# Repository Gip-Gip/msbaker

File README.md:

**Ms. Baker is a compact microcomputer built off the RP2040, specifically with model rocketry in mind.**
Occupying a footprint under 10cm&sup2;, this computer provides a unique density of many useful components, including a compact **25 pin GPIO** connector and a high accuracy **IMU**.
These features in a compact and light package is especially useful for low and medium power rockets, but may also find use in other applications where an ultra-small microcomputer may be needed.

## Feature Set

Ms. Baker is fairly feature packed for the size, and includes:

### RP2040 MCU

Powered by Raspberry Pi's RP2040 Microcontroller, Ms. Baker has the computation power of a 133MHz dual-core Arm Corted-M0+ processor in an unbelievably compact package.

### Micro SD Card Slot

Useful for logging data and loading/storing programs, Ms. Baker comes equipped with a compact MicroSD card slot for easy-to-use data storage.

### I2C IMU

No rocket computer should be complete with at least some form of telemetry, and Ms. Baker comes with the versitile LSM6DSO32 IMU, providing both gyro and acceleration data at a sample rate of up to 6.7kHz.
It has a maximum measurable acceleration range of &plusmn;32*g* and a maximum measurable angular rate of &plusmn;200dps, which should be good for most low and medium powered rockets, in theory.

### USB Programmable ROM

Thanks to the RP2040 Ms. Baker is entirely programmable via USB, meaning so long as you have a Micro USB cable and a computer you have access to **16MBytes of ROM** with no extra hardware!

### GPIO

Utilizing a Molex SlimStack connector Ms. Baker provides 25 pins of GPIO in a very compact footprint, completely up for any use the end user may desire!

### Robust Firmware

Like any other OpenApeShop project, Ms Baker's firmware is *(to be written)* in the Rust programming language, making it very robust and resistant to common bugs that may occur in other embedded firmware solutions.

## Development Status

**With a working prototype**, Ms. Baker is on it's third prototype and has the following steps that need to be completed before it is more or less ready for use:

- [ ] Program the firmware so that by default Ms. Baker acts as a telemetry logging device
- [ ] Field test Ms. Baker on a live rocket
- [ ] Reorganize PCB to fill up any unused space by
    - [ ] Spacing traces to reduce the chances of crosstalk, when possible
    - [ ] Increasing the size of traces to reduce impedence, when possible
- [ ] Document Ms. Baker so it's easy to use
- [ ] Develop a pin breakout board so prototyping is as easy as with a normal Raspberry Pi Pico

## Legal

Ms Baker's hardware is under the CERN-OHL-S and software under GPL-3.0.
See LEGAL-HARDWARE for all legal info regarding hardware, LEGAL-SOFTWARE for all legal info regarding software.

## Links

* [Website](https://openapeshop.org/hardware/msbaker)
* [Schematic](https://github.com/Gip-Gip/msbaker/raw/main/docs/Renders/schematic.png)

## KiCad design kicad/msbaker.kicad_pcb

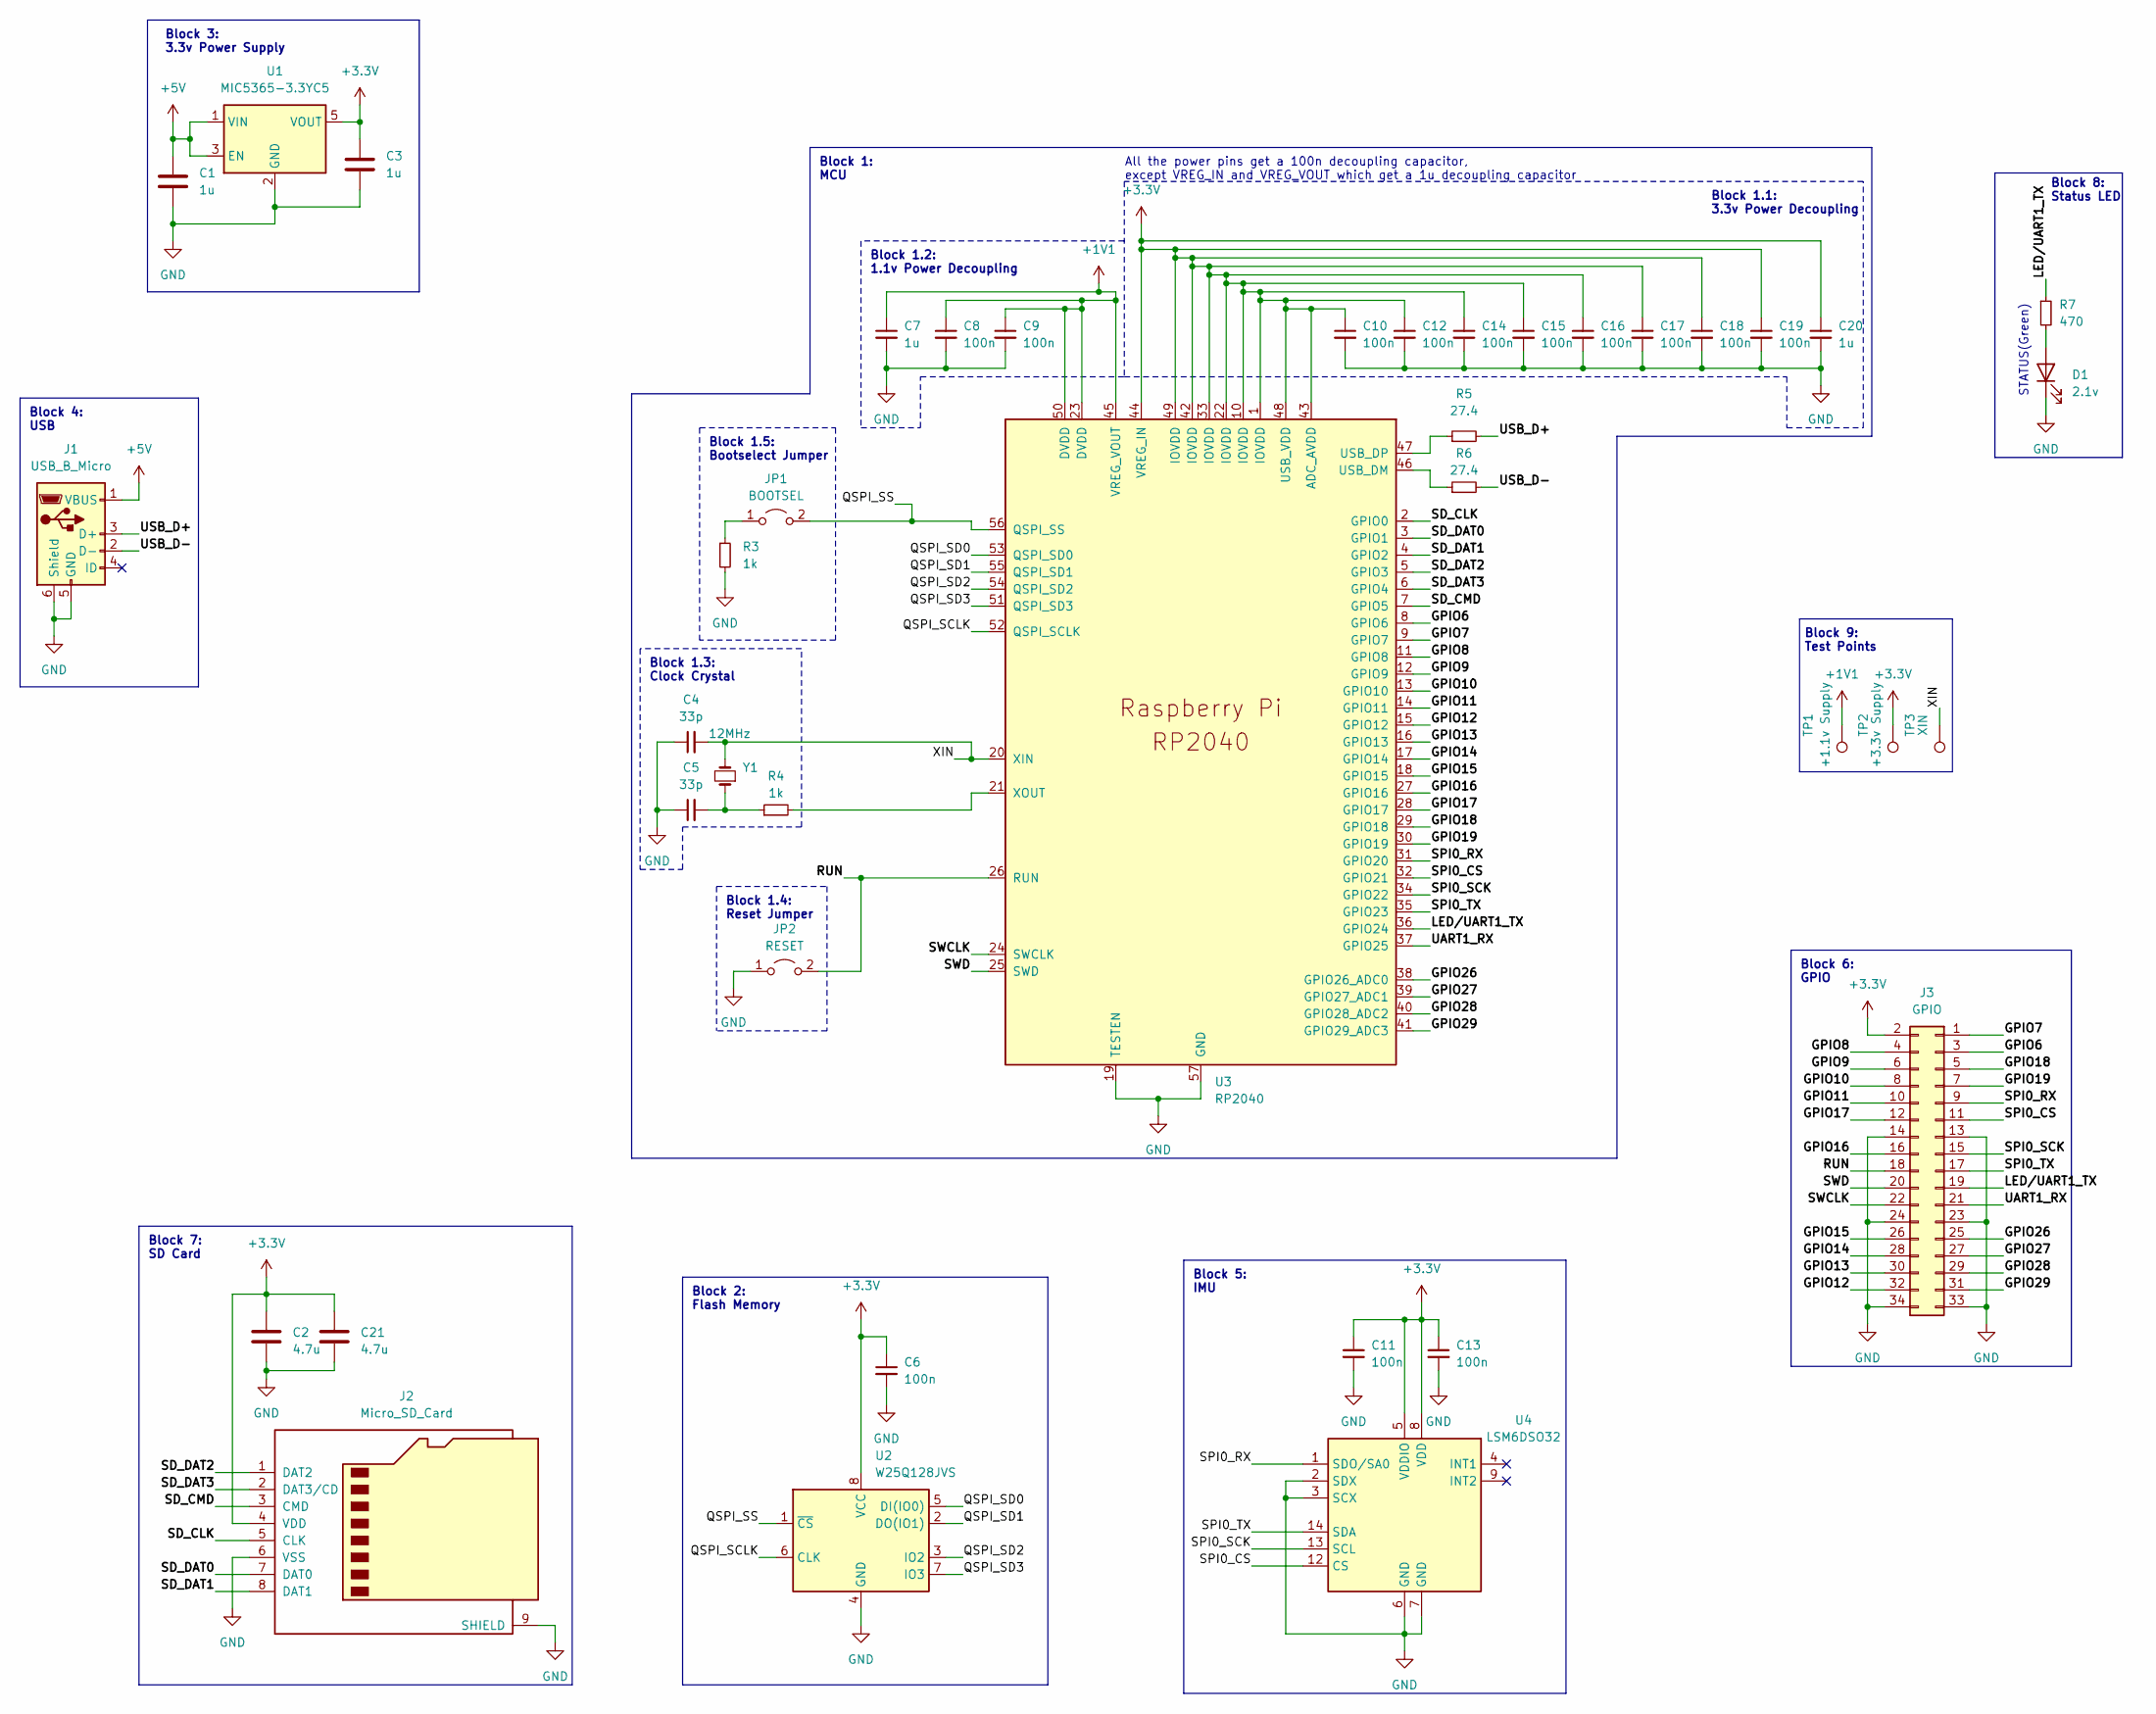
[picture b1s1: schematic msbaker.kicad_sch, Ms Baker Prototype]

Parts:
C1, C3, C7, C20: 1u; C_0402_1005Metric; MPN C1005X5R1E105K050BE
C2, C21: 4.7u; C_0402_1005Metric; MPN C1005X5R1A475K050BE
C4, C5: 33p; C_0402_1005Metric; MPN CGA2B2C0G1H330J050BA
C6, C8, C9, C10, C11, C12, C13, C14, C15, C16, C17, C18, C19: 100n; C_0402_1005Metric; MPN C1005X7R1H104K050BE
D1: 2.1v; LED_0402_1005Metric; MPN APHHS1005CGCK
J1: USB_B_Micro; USB_Micro-B_Molex-105017-0001; MPN 105017-0001
J2: Micro_SD_Card; microSD_HC_Molex_104031-0811; MPN 104031-0811
J3: GPIO; 5055513420; MPN 505551-3420
JP1: BOOTSEL; poke_jumper
JP2: RESET; poke_jumper
R3, R4: 1k; R_0402_1005Metric; MPN AC0402FR-071KL
R5, R6: 27.4; R_0402_1005Metric; MPN AC0402FR-0727R4L
R7: 470; R_0402_1005Metric; MPN AC0402FR-07120RL
TP1: +1.1v Supply; TestPoint_Pad_1.0x1.0mm
TP2: +3.3v Supply; TestPoint_Pad_1.0x1.0mm
TP3: XIN; TestPoint_Pad_1.0x1.0mm
U1: MIC5365-3.3YC5; SOT-353_SC-70-5; MPN MIC5365-3.3YC5-TR
U2: W25Q128JVS; SOIC-8_5.23x5.23mm_P1.27mm; MPN W25Q128JVSIM TR
U3: RP2040; RP2040-QFN-56; MPN RP2040TR13
U4: LSM6DSO32; LGA-14_3x2.5mm_P0.5mm_LayoutBorder3x4y; MPN LSM6DSO32TR
Y1: 12MHz; Crystal_SMD_5032-2Pin_5.0x3.2mm; MPN 445I23D12M00000

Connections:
+1V1: C7.1, C8.1, C9.1, TP1.1, U3.23 (DVDD), U3.45 (VREG_VOUT), U3.50 (DVDD)
+3.3V: C2.1, C3.1, C6.1, C10.1, C11.1, C12.1, C13.1, C14.1, C15.1, C16.1, C17.1, C18.1, C19.1, C20.1, C21.1, J2.4 (VDD), J3.2, TP2.1, U1.5 (VOUT), U2.8 (VCC), U3.1 (IOVDD), U3.10 (IOVDD), U3.22 (IOVDD), U3.33 (IOVDD), U3.42 (IOVDD), U3.43 (ADC_AVDD), U3.44 (VREG_IN), U3.48 (USB_VDD), U3.49 (IOVDD), U4.5 (VDDIO), U4.8 (VDD)
+5V: C1.1, J1.1 (VBUS), U1.1 (VIN), U1.3 (EN)
/GPIO6: J3.3, U3.8 (GPIO6)
/GPIO7: J3.1, U3.9 (GPIO7)
/GPIO8: J3.4, U3.11 (GPIO8)
/GPIO9: J3.6, U3.12 (GPIO9)
/GPIO10: J3.8, U3.13 (GPIO10)
/GPIO11: J3.10, U3.14 (GPIO11)
/GPIO12: J3.32, U3.15 (GPIO12)
/GPIO13: J3.30, U3.16 (GPIO13)
/GPIO14: J3.28, U3.17 (GPIO14)
/GPIO15: J3.26, U3.18 (GPIO15)
/GPIO16: J3.16, U3.27 (GPIO16)
/GPIO17: J3.12, U3.28 (GPIO17)
/GPIO18: J3.5, U3.29 (GPIO18)
/GPIO19: J3.7, U3.30 (GPIO19)
/GPIO26: J3.25, U3.38 (GPIO26_ADC0)
/GPIO27: J3.27, U3.39 (GPIO27_ADC1)
/GPIO28: J3.29, U3.40 (GPIO28_ADC2)
/GPIO29: J3.31, U3.41 (GPIO29_ADC3)
/LED/UART1_TX: J3.19, R7.1, U3.36 (GPIO24)
/QSPI_SCLK: U2.6 (CLK), U3.52 (QSPI_SCLK)
/QSPI_SD0: U2.5 (DI(IO0)), U3.53 (QSPI_SD0)
/QSPI_SD1: U2.2 (DO(IO1)), U3.55 (QSPI_SD1)
/QSPI_SD2: U2.3 (IO2), U3.54 (QSPI_SD2)
/QSPI_SD3: U2.7 (IO3), U3.51 (QSPI_SD3)
/QSPI_SS: JP1.2 (B), U2.1 (~CS), U3.56 (QSPI_SS); also elsewhere on the board
/RUN: J3.18, JP2.2 (B), U3.26 (RUN); also elsewhere on the board
/SD_CLK: J2.5 (CLK), U3.2 (GPIO0)
/SD_CMD: J2.3 (CMD), U3.7 (GPIO5)
/SD_DAT0: J2.7 (DAT0), U3.3 (GPIO1)
/SD_DAT1: J2.8 (DAT1), U3.4 (GPIO2)
/SD_DAT2: J2.1 (DAT2), U3.5 (GPIO3)
/SD_DAT3: J2.2 (DAT3/CD), U3.6 (GPIO4)
/SPI0_CS: J3.11, U3.32 (GPIO21), U4.12 (CS)
/SPI0_RX: J3.9, U3.31 (GPIO20), U4.1 (SDO/SA0)
/SPI0_SCK: J3.15, U3.34 (GPIO22), U4.13 (SCL)
/SPI0_TX: J3.17, U3.35 (GPIO23), U4.14 (SDA)
/SWCLK: J3.22, U3.24 (SWCLK)
/SWD: J3.20, U3.25 (SWD)
/UART1_RX: J3.21, U3.37 (GPIO25)
/USB_D+: J1.3 (D+), R5.2
/USB_D-: J1.2 (D-), R6.2
/XIN: C4.2, TP3.1, U3.20 (XIN), Y1.2
GND: C1.2, C2.2, C3.2, C4.1, C5.1, C6.2, C7.2, C8.2, C9.2, C10.2, C11.2, C12.2, C13.2, C14.2, C15.2, C16.2, C17.2, C18.2, C19.2, C20.2, C21.2, D1.1 (K), J1.5 (GND), J1.6 (Shield), J2.6 (VSS), J2.9 (SHIELD), J3.13, J3.14, J3.23, J3.24, J3.33, J3.34, J3.GND, JP2.1 (A), R3.2, U1.2 (GND), U2.4 (GND), U3.19 (TESTEN), U3.57 (GND), U4.2 (SDX), U4.3 (SCX), U4.6 (GND), U4.7 (GND); also elsewhere on the board
unnamed: C5.2, R4.1, Y1.1
unnamed: D1.2 (A), R7.2
unnamed 48: JP1.1 (A), R3.1; also elsewhere on the board
unnamed: R6.1, U3.46 (USB_DM)
unnamed: R5.1, U3.47 (USB_DP)
unnamed: R4.2, U3.21 (XOUT)

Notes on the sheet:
STATUS(Green)
Block 1: MCU
Block 5: IMU
Block 3: 3.3v Power Supply
Block 4: USB
Block 7: SD Card
Block 1.3: Clock Crystal
Block 1.5: Bootselect Jumper
Block 6: GPIO
Block 1.2: 1.1v Power Decoupling
Block 1.1: 3.3v Power Decoupling
All the power pins get a 100n decoupling capacitor, except VREG_IN and VREG_VOUT which get a 1u decoupling capacitor
Block 8: Status LED
Block 2: Flash Memory
Block 9: Test Points
Block 1.4: Reset Jumper

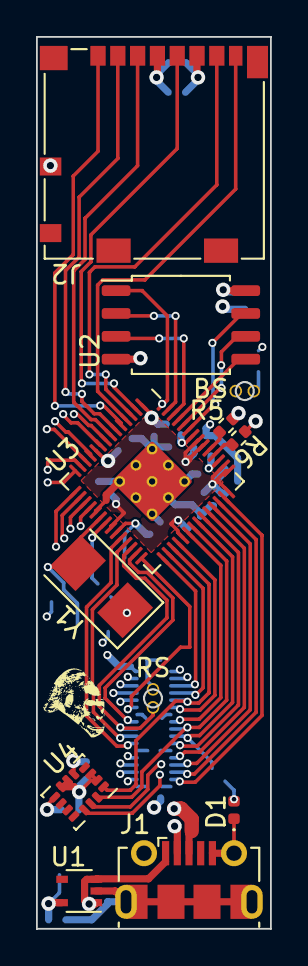
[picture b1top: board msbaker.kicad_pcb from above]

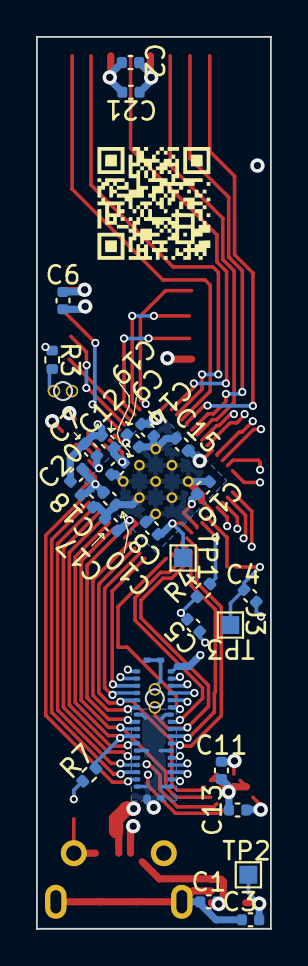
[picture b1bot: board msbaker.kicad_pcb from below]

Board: 4 copper layers, 13.0 x 49.5 mm, 40 parts (28 on the bottom side), 52 nets.

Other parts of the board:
BS: BOOTSEL; poke_jumper
RS: RESET; poke_jumper

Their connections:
/QSPI_SS: BS.2 (B); also elsewhere on the board
/RUN: RS.2 (B); also elsewhere on the board
GND: RS.1 (A); also elsewhere on the board
unnamed 48: BS.1 (A); also elsewhere on the board

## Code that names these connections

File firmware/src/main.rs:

//! Main functions and other top-level code needed to operate

// Copyright (c) 2023 Charles M. Thompson
//
// This file is part of Ms. Baker's firmware.
//
// Ms. Baker's firmware is free software: you can redistribute it and/or modify it under
// the terms only of version 3 of the GNU General Public License as published
// by the Free Software Foundation
//
// Ms. Baker's firmware is distributed in the hope that it will be useful, but WITHOUT ANY
// WARRANTY; without even the implied warranty of MERCHANTABILITY or FITNESS
// FOR A PARTICULAR PURPOSE. See the GNU General Public License
// for more details.
//
// You should have received a copy of the GNU General Public License along with
// Ms. Baker's firmware(in a file named COPYING).
// If not, see <https://www.gnu.org/licenses/>.

#![cfg_attr(not(test), no_std)]
#![no_main]

mod sdio;

use crate::sdio::Sdio4bit;

use rp2040_hal as hal;

use core::panic::PanicInfo;
use hal::pac;

use hal::pio::PIOExt;
use embedded_hal::blocking::i2c::WriteRead;
use fugit::RateExtU32;

use embedded_hal::digital::v2::OutputPin;
use rp2040_hal::clocks::Clock;
use cortex_m::delay::Delay;

#[link_section = ".boot2"]
#[used]
pub static BOOT2: [u8; 256] = rp2040_boot2::BOOT_LOADER_GENERIC_03H;

const XTAL_FREQ_HZ: u32 = 12_000_000u32;
const IMU_ADDR: u8 = 0b1101010;
const IMU_CHECK_REG: u8 = 0x0F;
const IMU_CHECK_VAL: u8 = 0b01101100;

/// Core 0 main function, the entrypoint for our code
/// Everything starts here!
#[rp2040_hal::entry]
fn main_0() -> ! {
    // ===================================================================== //
    // STEP 1, INITIALIZATION!                                               //
    // ===================================================================== //
    let mut pac = pac::Peripherals::take().unwrap();
    let core = pac::CorePeripherals::take().unwrap();

    let mut watchdog = hal::Watchdog::new(pac.WATCHDOG);

    let clocks = hal::clocks::init_clocks_and_plls(
        XTAL_FREQ_HZ,
        pac.XOSC,
        pac.CLOCKS,
        pac.PLL_SYS,
        pac.PLL_USB,
        &mut pac.RESETS,
        &mut watchdog,
    )
    .ok()
    .unwrap();

    let sio = hal::Sio::new(pac.SIO);

    let pins = hal::gpio::Pins::new(
        pac.IO_BANK0,
        pac.PADS_BANK0,
        sio.gpio_bank0,
        &mut pac.RESETS,
    );

    // Initialize GPIO
    //let mut pin_led = pins.gpio25.into_push_pull_output();
    // Initialize the I2C1 line
    // !TODO! says it's I2C0 on the schematic, figure out why
    let pin_i2c1_sda = pins.gpio6.into_mode::<hal::gpio::FunctionI2C>();
    let pin_i2c1_scl = pins.gpio7.into_mode::<hal::gpio::FunctionI2C>();
    let mut i2c1 = hal::I2C::i2c1(
        pac.I2C1,
        pin_i2c1_sda,
        pin_i2c1_scl,
        400.kHz(),
        &mut pac.RESETS,
        &clocks.system_clock,
    );

    // Initialize the SD card pins
    let pin_sd_clk = pins.gpio0.into_mode::<hal::gpio::FunctionPio0>(); 
    let pin_sd_cmd = pins.gpio5.into_mode::<hal::gpio::FunctionPio0>();
    let pin_sd_dat0 = pins.gpio1.into_mode::<hal::gpio::FunctionPio0>();
    let pin_sd_dat1 = pins.gpio2.into_mode::<hal::gpio::FunctionPio0>();
    let pin_sd_dat2 = pins.gpio3.into_mode::<hal::gpio::FunctionPio0>();
    let pin_sd_dat3 = pins.gpio4.into_mode::<hal::gpio::FunctionPio0>();

    // Get their ids
    let pin_sd_clk_id = pin_sd_clk.id().num;
    let pin_sd_cmd_id = pin_sd_cmd.id().num;
    let pin_sd_dat0_id = pin_sd_dat0.id().num;
    let pin_sd_dat1_id = pin_sd_dat1.id().num;
    let pin_sd_dat2_id = pin_sd_dat2.id().num;
    let pin_sd_dat3_id = pin_sd_dat3.id().num;

    // Initialize the sd card
    let (mut pio, sm0, sm1, _, _) = pac.PIO0.split(&mut pac.RESETS);
    let mut delay = Delay::new(core.SYST, clocks.system_clock.freq().to_Hz());
    let mut sd_controller = Sdio4bit::new(
        pio,
        delay,
        sm0,
        sm1,
        pin_sd_clk_id,
        pin_sd_cmd_id, 
        pin_sd_dat0_id,
        pin_sd_dat1_id,
        pin_sd_dat2_id,
        pin_sd_dat3_id
    );

    sd_controller.init();

    // ===================================================================== //
    // STEP 1.1, SELF CHECKS!                                                //
    // ===================================================================== //

    // Check the IMU
    let mut response: [u8; 1] = [0; 1];
    // Remember you have to write to i2c to read from i2c...
    i2c1.write_read(IMU_ADDR, &[IMU_CHECK_REG], &mut response)
        .unwrap();

    if response[0] != IMU_CHECK_VAL {
        panic!("IMU NOT OK");
    }

    // !TODO! Self check for sd card
    


    // !TODO! Initialize core 1

    // ===================================================================== //
    // STEP 2, WAIT!                                                         //
    // ===================================================================== //

    // Turn the LED solid to signify all is good!
    //pin_led.set_high().unwrap();

    loop {
        cortex_m::asm::wfi();
    }
}

/// Core 1 main function, called by core 0
fn main_1() {
    todo!()
}

#[panic_handler]
fn panic(_: &PanicInfo) -> ! {
    loop {}
}

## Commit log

2021-01-11 Basic Arduino/Eclipse setup initialized
2021-01-19 Added RN4871 functionality
2021-01-19 Added test functionality
2021-01-21 Added circuit board and design docs
2021-01-21 Added PDF of current schematic
2021-01-27 Schematic completed, documentation in progress
2021-02-19 Adjusted 3 wire UART and removed 3/4 the ram
2021-03-30 Finished revision 1 schematic
2021-04-16 Finalized prototype and prototype BOM
2021-05-05 Updated source code, currently untested
2021-05-12 Finished test UART program
2021-05-19 Total schematic redesign
2021-05-24 Rough draft of revision 2.1 schematic
2021-06-20 Finalized 2.3.1 prototype
2021-06-27 Created README
2021-07-14 Added GOALS
2021-07-20 Started revision 2.4.0
2021-07-20 Set theme jekyll-theme-minimal
2021-07-20 Modified PCB edge connectors
2021-08-16 Started work on the website and revision 2.4.0
2021-08-16 Added a link to the website
2022-08-05 Updated readme for start of revision 3
2022-08-12 Started laying out specifications for Ms. Baker v3
2022-08-13 Updating general specifications
2022-08-14 Continuing work on defining the Ms. Baker General Specifications
2022-08-14 Completed RP2040 power decoupling circuitry
2022-08-14 Added clock crystal block
2022-08-15 Added flash memory block
2022-08-15 Added 3.3v power supply block
2022-08-15 Added imu block
2022-08-18 Added USB block
2022-08-18 Added SD Card Block
2022-08-18 Added in-series resistors for the USB data lines
2022-08-18 Added gpio block
2022-08-18 Changed the layout of the schematic
2022-08-19 Assigned footprints
2022-08-19 Applied footprints + Added LED block + Created design checklist
2022-08-19 Corrected small mistake where I2C0 was placed on GPIO8 and GPIO9 instead of chip pin 8 and 9
2022-08-20 Created BOM
2022-08-20 Corrected block numbers
2022-08-20 Fixed typo in schematic
2022-08-21 Added pcb files
2022-08-25 Fixed references on silkscreen layer
2022-08-25 Added reset jumper block
2022-08-25 Separated the bootsel jumper into it's own block
2022-08-25 Updated BOM
2022-08-25 Added reset jumper to PCB
2022-08-25 Fixed DRC violations
2022-08-25 Added M2 screw holes to the solder paste layer to give points to align the solder paste stencil
2022-08-26 Changed status led resistor to 480 to improve efficiency
2022-08-26 Added test points to schematic
2022-08-26 Corrected typo on schematic
2023-02-19 Updated to v3
2023-02-28 Created Hello World firmware
2023-03-01 Added dual core schema and removed old 2.3.1 files
2023-03-02 Added IMU self check
2023-03-02 Changed to GPL-3.0 and CERN OHL 2
2023-03-08 Started implementation of SDIO, unknown and scary bugs occuring!
2023-03-08 Updated delay time to 500ms, still scary
2023-03-31 Migrated firmware to msbaker-firmware
2023-05-17 Changed IMU to SPI and shrunk board
